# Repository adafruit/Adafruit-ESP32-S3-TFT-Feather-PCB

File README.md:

## Adafruit ESP32-S3 TFT Feather PCB

<a href="http://www.adafruit.com/products/5483"><br/>
Click here to purchase one from the Adafruit shop</a>

PCB files for the Adafruit ESP32-S3 TFT Feather. 

Format is EagleCAD schematic and board layout
* https://www.adafruit.com/product/5483

### Description

We've got a new machine here at Adafruit, it can uncover your deepest desires. Don't believe me? I'll turn it on right now to prove it to you! What, you want your very own soft serve ice cream machine? OK well, that's not something we can provide. But we can provide your second-deepest desire: an ESP32-S3 Feather board with a built in IPS TFT color display. It's got all the ~~delicious creamy goodness~~ features of a Feather main board, the comforting warmth of an ESP32-S3 WiFi+BLE microcontroller, and the crispness of a 240x135 pixel color TFT display. All that and it will even plug in nicely into a breadboard, terminal block wing, or Feather Doubler or even just stack on top of another wing.

This Feather comes with native USB and 4 MB Flash + 2 MB of PSRAM, so it is perfect for use with CircuitPython or Arduino with low-cost WiFi. Native USB means it can act like a keyboard or a disk drive. WiFi means it's awesome for IoT projects. And Feather means it works with the large community of Feather Wings for expandability.

The ESP32-S3 is a highly-integrated, low-power, 2.4 GHz Wi-Fi/BLE System-on-Chip (SoC) solution that has built-in native USB as well as some other interesting new technologies like Time of Flight distance measurements and AI acceleration. With its state-of-the-art power and RF performance, this SoC is an ideal choice for a wide variety of application scenarios relating to the Internet of Things (IoT), wearable electronics, and smart homes.

The Feather ESP32-S3 has a dual-core 240 MHz chip, so it is comparable to ESP32's dual-core. However, there is no Bluetooth Classic support, only Bluetooth LE. This chip is a great step up from the earlier ESP32-S2! This ESP32-S3 mini-module we are using on the Feather comes with 4 MB flash and 2 MB PSRAM, as well as lots of 512KB of SRAM so it's perfect for use with CircuitPython support or any time massive buffers are needed: for fast memory access use SRAM, for slower-but-roomier access use PSRAM. It's also great for use in ESP-IDF or with Arduino support.

The color TFT is connected to the SPI pins and uses additional pins for control that are not exposed to the breakout pads. It's the same display as you see here, with 240x135 pixels and is IPS so you get bright color at any angle. The backlight is also connected to a separate pin so you can PWM the backlight up and down as desired.

For low power usages, the Feather has a second low-dropout 3.3V regulator. The regulator is controlled with a GPIO pin on the enable line and can shut off power to the Stemma QT port and TFT. There is also a separate power pin for the NeoPixel that can be used to disable it for even lower quiescent power. With everything off and in deep sleep mode, the TFT feather uses about 100uA of current.

### License

Adafruit invests time and resources providing this open source design, please support Adafruit and open-source hardware by purchasing products from [Adafruit](https://www.adafruit.com)!

Designed by Limor Fried/Ladyada for Adafruit Industries.

Creative Commons Attribution/Share-Alike, all text above must be included in any redistribution. 
See license.txt for additional details.

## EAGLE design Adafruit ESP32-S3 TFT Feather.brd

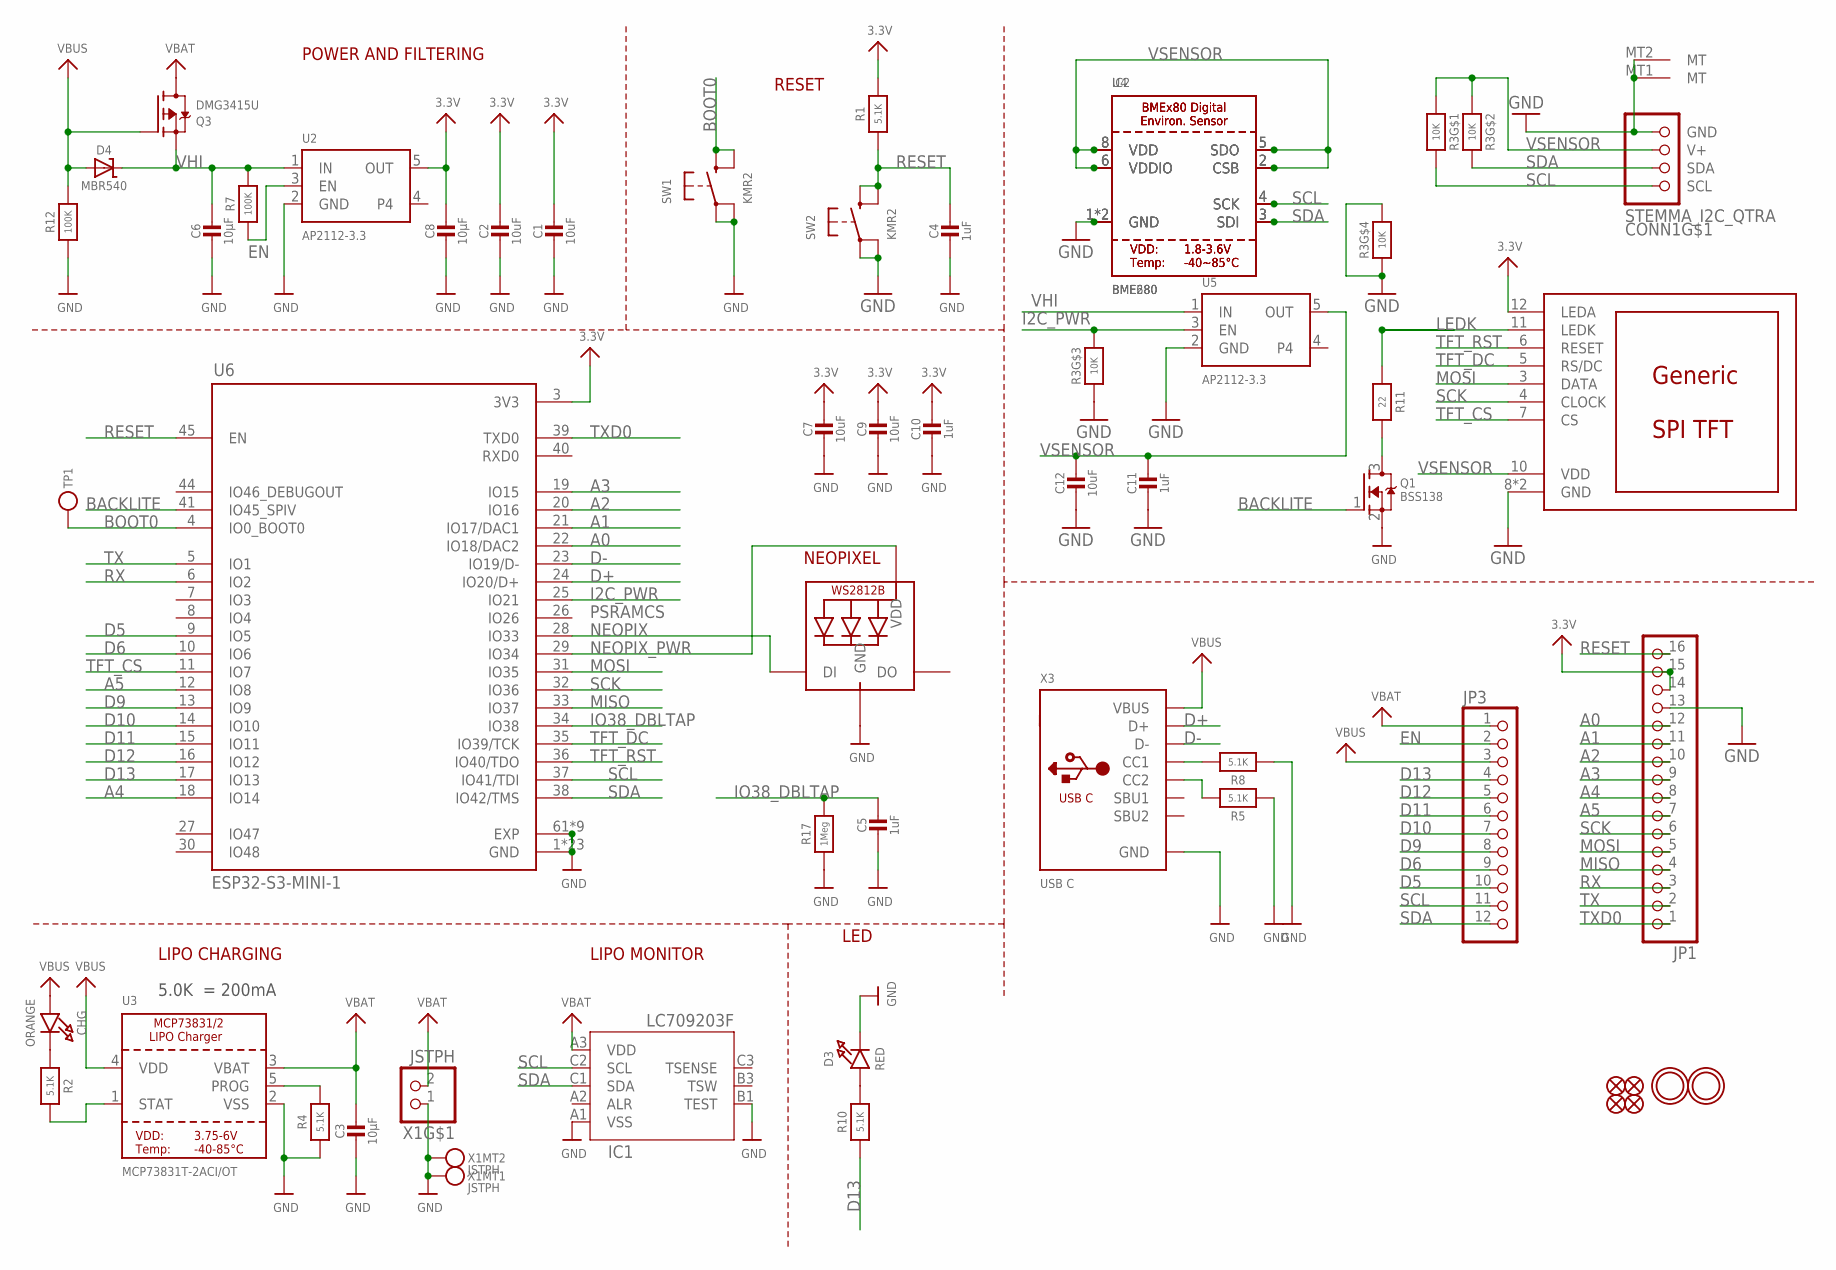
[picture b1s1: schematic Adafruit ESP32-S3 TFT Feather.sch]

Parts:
C1, C2, C7, C9, C12: 10uF; 0805-NO
C3, C6, C8: 10µF; 0805-NO
C4, C5, C10, C11: 1uF; 0603-NO
CHG: ORANGE; CHIPLED_0603_NOOUTLINE
CONN1: STEMMA_I2C_QTRA; JST_SH4_RA
D3: RED; CHIPLED_0603_NOOUTLINE
D4: MBR540; SOD-123
DISP1: DISP_LCD_GENERIC_SPI_1.14IN_240X135_WRAPUNDER; TFT_1.14IN_240X135_WRAPUNDER
IC1: LC709203F/MH; WLCSP9
IC2: BME680
JP1: HEADER-1X16_MIN; 1X16_ROUND_MIN
JP3: HEADER-1X12_MIN; 1X12_ROUND_MIN
LED1: WS2812B_SK6805_1515; SK6805_1515
Q1: BSS138; SOT23-R
Q3: DMG3415U; SOT23-R
R1, R2, R4, R5, R8, R10: 5.1K; 0603-NO
R3: 10K; RESPACK_4X0603
R7, R12: 100K; 0603-NO
R11: 22; 0603-NO
R17: 1Meg; 0603-NO
SW1, SW2: KMR2; BTN_KMR2_4.6X2.8
TP1: TESTPOINTROUND1.5MMNO; TESTPOINT_ROUND_1.5MM_NO
U2, U5: AP2112-3.3; SOT23-5
U3: MCP73831T-2ACI/OT; SOT23-5
U4: BME280
U6: ESP32-S3-MINI-1; QFN60_ESP32-S2-MINI-1_EXP
U$31, U$32: MOUNTINGHOLE2.5; MOUNTINGHOLE_2.5_PLATED
U$34, U$35, U$55, U$56: FIDUCIAL_1MM
X1: JSTPH; JSTPH2_BATT
X3: USB C; USB_C_CUSB31-CFM2AX-01-X

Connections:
3.3V: C1.1, C2.1, C7.1, C8.1, C9.1, C10.1, DISP1.12 (LEDA), JP1.14, JP1.15, R1.2, U2.5 (OUT), U6.3 (3V3)
A0: JP1.12, U6.22 (IO18/DAC2)
A1: JP1.11, U6.21 (IO17/DAC1)
A2: JP1.10, U6.20 (IO16)
A3: JP1.9, U6.19 (IO15)
A4: JP1.8, U6.18 (IO14)
A5: JP1.7, U6.12 (IO8)
BACKLITE: Q1.1 (G), U6.41 (IO45_SPIV)
BOOT0: SW1.B (S), SW1.B' (S1), TP1.P$1, U6.4 (IO0_BOOT0)
D5: JP3.10, U6.9 (IO5)
D6: JP3.9, U6.10 (IO6)
D9: JP3.8, U6.13 (IO9)
D10: JP3.7, U6.14 (IO10)
D11: JP3.6, U6.15 (IO11)
D12: JP3.5, U6.16 (IO12)
D13: JP3.4, R10.1, U6.17 (IO13)
D+: U6.24 (IO20/D+), X3.A6 (D+), X3.B6 (D+)
D-: U6.23 (IO19/D-), X3.A7 (D-), X3.B7 (D-)
EN: JP3.2, R7.1, U2.3 (EN)
GND: C1.2, C2.2, C3.2, C4.2, C5.2, C6.2, C7.2, C8.2, C9.2, C10.2, C11.2, C12.2, CONN1.1 (GND), CONN1.MT1 (MT), CONN1.MT2 (MT), D3.C, DISP1.8 (GND), DISP1.13 (GND), IC1.A1 (VSS), IC1.B1 (TEST), IC2.1 (GND), IC2.7 (GND), JP1.13, LED1.4 (GND), Q1.2 (S), R3.3 (1), R3.4 (1), R3.5 (2), R4.1, R5.1, R8.1, R12.1, R17.1, SW1.A, SW1.A' (P1), SW2.A, SW2.A' (P1), U2.2 (GND), U3.2 (VSS), U4.1 (GND), U4.7 (GND), U5.2 (GND), U6.1 (GND), U6.2 (GND), U6.42 (GND), U6.43 (GND), U6.46 (GND), U6.47 (GND), U6.48 (GND), U6.49 (GND), U6.50 (GND), U6.51 (GND), U6.52 (GND), U6.53 (GND), U6.54 (GND), U6.55 (GND), U6.56 (GND), U6.57 (GND), U6.58 (GND), U6.59 (GND), U6.60 (GND), U6.61 (EXP), U6.62 (GND), U6.63 (GND), U6.64 (GND), U6.65 (GND), U6.66 (EXP), U6.67 (EXP), U6.68 (EXP), U6.69 (EXP), U6.70 (EXP), U6.71 (EXP), U6.72 (EXP), U6.73 (EXP), X1.1, X1.NC1, X1.NC2, X3.A1B12 (GND), X3.B1A12 (GND)
I2C_PWR: R3.6 (2), U5.3 (EN), U6.25 (IO21)
IO38_DBLTAP: C5.1, R17.2, U6.34 (IO38)
LEDK: DISP1.11 (LEDK), R11.1
MISO: JP1.4, U6.33 (IO37)
MOSI: DISP1.3 (DATA), JP1.5, U6.31 (IO35)
unnamed: CHG.C, R2.1
unnamed: Q1.3 (D), R11.2
unnamed: R2.2, U3.1 (STAT)
unnamed: R4.2, U3.5 (PROG)
unnamed: D3.A, R10.2
unnamed: R8.2, X3.A5 (CC1)
unnamed: R5.2, X3.B5 (CC2)
NEOPIX: LED1.1 (DI), U6.28 (IO33)
NEOPIX_PWR: LED1.2 (VDD), U6.29 (IO34)
RESET: C4.1, JP1.16, R1.1, SW2.B (S), SW2.B' (S1), U6.45 (EN)
RX: JP1.3, U6.6 (IO2)
SCK: DISP1.4 (CLOCK), JP1.6, U6.32 (IO36)
SCL: CONN1.4 (SCL), IC1.C2 (SCL), IC2.4 (SCK), JP3.11, R3.8 (2), U4.4 (SCK), U6.37 (IO41/TDI)
SDA: CONN1.3 (SDA), IC1.C1 (SDA), IC2.3 (SDI), JP3.12, R3.7 (2), U4.3 (SDI), U6.38 (IO42/TMS)
TFT_CS: DISP1.7 (CS), U6.11 (IO7)
TFT_DC: DISP1.5 (RS/DC), U6.35 (IO39/TCK)
TFT_RST: DISP1.6 (RESET), U6.36 (IO40/TDO)
TX: JP1.2, U6.5 (IO1)
TXD0: JP1.1, U6.39 (TXD0)
VBAT: C3.1, IC1.A3 (VDD), JP3.1, Q3.3 (D), U3.3 (VBAT), X1.2
VBUS: CHG.A, D4.A, JP3.3, Q3.1 (G), R12.2, U3.4 (VDD), X3.A4B9 (VBUS), X3.B4A9 (VBUS)
VHI: C6.1, D4.C, Q3.2 (S), R7.2, U2.1 (IN), U5.1 (IN)
VSENSOR: C11.1, C12.1, CONN1.2 (V+), DISP1.10 (VDD), IC2.2 (CSB), IC2.5 (SDO), IC2.6 (VDDIO), IC2.8 (VDD), R3.1, R3.2 (1), U4.2 (CSB), U4.5 (SDO), U4.6 (VDDIO), U4.8 (VDD), U5.5 (OUT)

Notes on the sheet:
POWER AND FILTERING
RESET
5.0K = 200mA
LIPO CHARGING
LED
PSRAMCS
NEOPIXEL
LIPO MONITOR

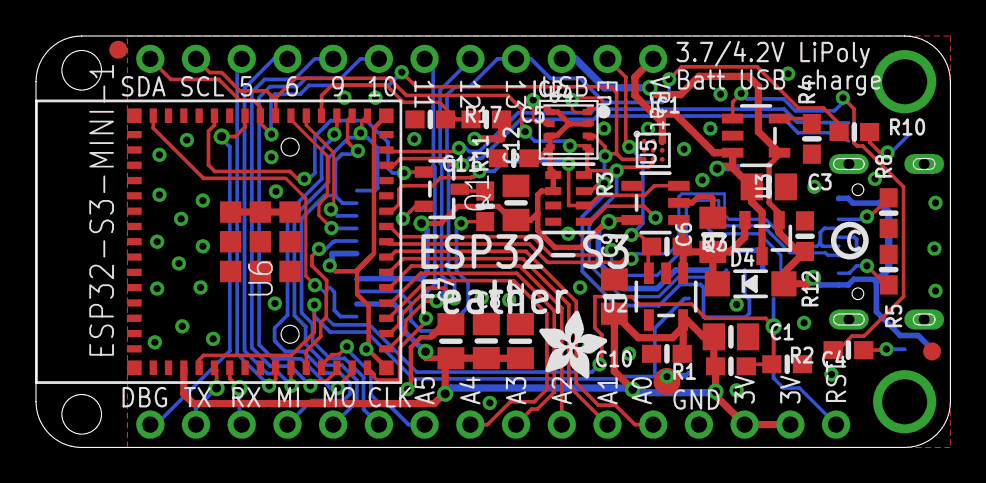
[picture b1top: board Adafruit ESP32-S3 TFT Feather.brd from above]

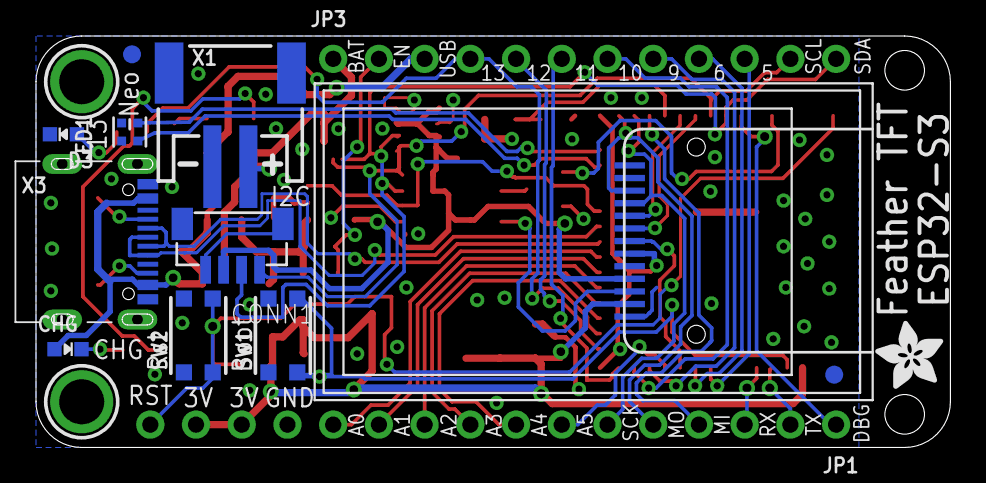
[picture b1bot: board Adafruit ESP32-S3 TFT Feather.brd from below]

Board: 2 copper layers, 50.8 x 22.9 mm, 54 parts (16 on the bottom side), 48 nets.

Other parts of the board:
U$7: PCBFEAT-REV-040
U$9, U$54: ADAFRUIT_3.5MM

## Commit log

2022-07-05 Added board files
2022-08-11 Add PrettyPins.
2022-08-12 Add factory reset and bootloader files.
2023-06-08 updating factory reset files
2023-06-10 Updating bin file
    Replacing incorrect bin file
2024-02-07 update pinout pdf

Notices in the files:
parts and their libraries:
microbuilder: This work is placed in the public domain, and may be freely used for commercial and non-commercial work with the following conditions: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
COPYRIGHT: Copyright (C) 2018 Accelerated Designs. All rights reserved
